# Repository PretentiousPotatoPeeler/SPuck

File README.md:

# PCB Parts

| Block | Part | JLCPCB |
| ------|------|--------|
| ESP32 | ESP32-S3-WROOM-1-N16R8 | [C2913202](https://jlcpcb.com/partdetail/3198300-ESP32_S3_WROOM_1N16R8/C2913202) |
| Mic 2X | SD18OB261-060 | [C2895290](https://jlcpcb.com/partdetail/Goertek-SD18OB261060/C2895290) |
| Amp   | MAX98357AETE+T | [C910544](https://jlcpcb.com/partdetail/978950-MAX98357AETET/C910544) |
| USB-C | HC-TYPE-C-16P-CH2.58-3A-02 | [C5307759](https://jlcpcb.com/partdetail/Hctl-HC_TYPE_C_16P_CH2_58_3A02/C5307759) |
| Power Regulation | AMS1117 | [C347222](https://jlcpcb.com/partdetail/323882-AMS1117_33/C347222) |
| Screw Terminal | XY308-2.54-2P | [C557685](https://jlcpcb.com/partdetail/Ningbo_Xinlaiya_elec-XY308_2_542P/C557685) |
| TVS | LESD5D5.0CT1G | [C383211](https://jlcpcb.com/partdetail/Lrc-LESD5D50CT1G/C383211) |

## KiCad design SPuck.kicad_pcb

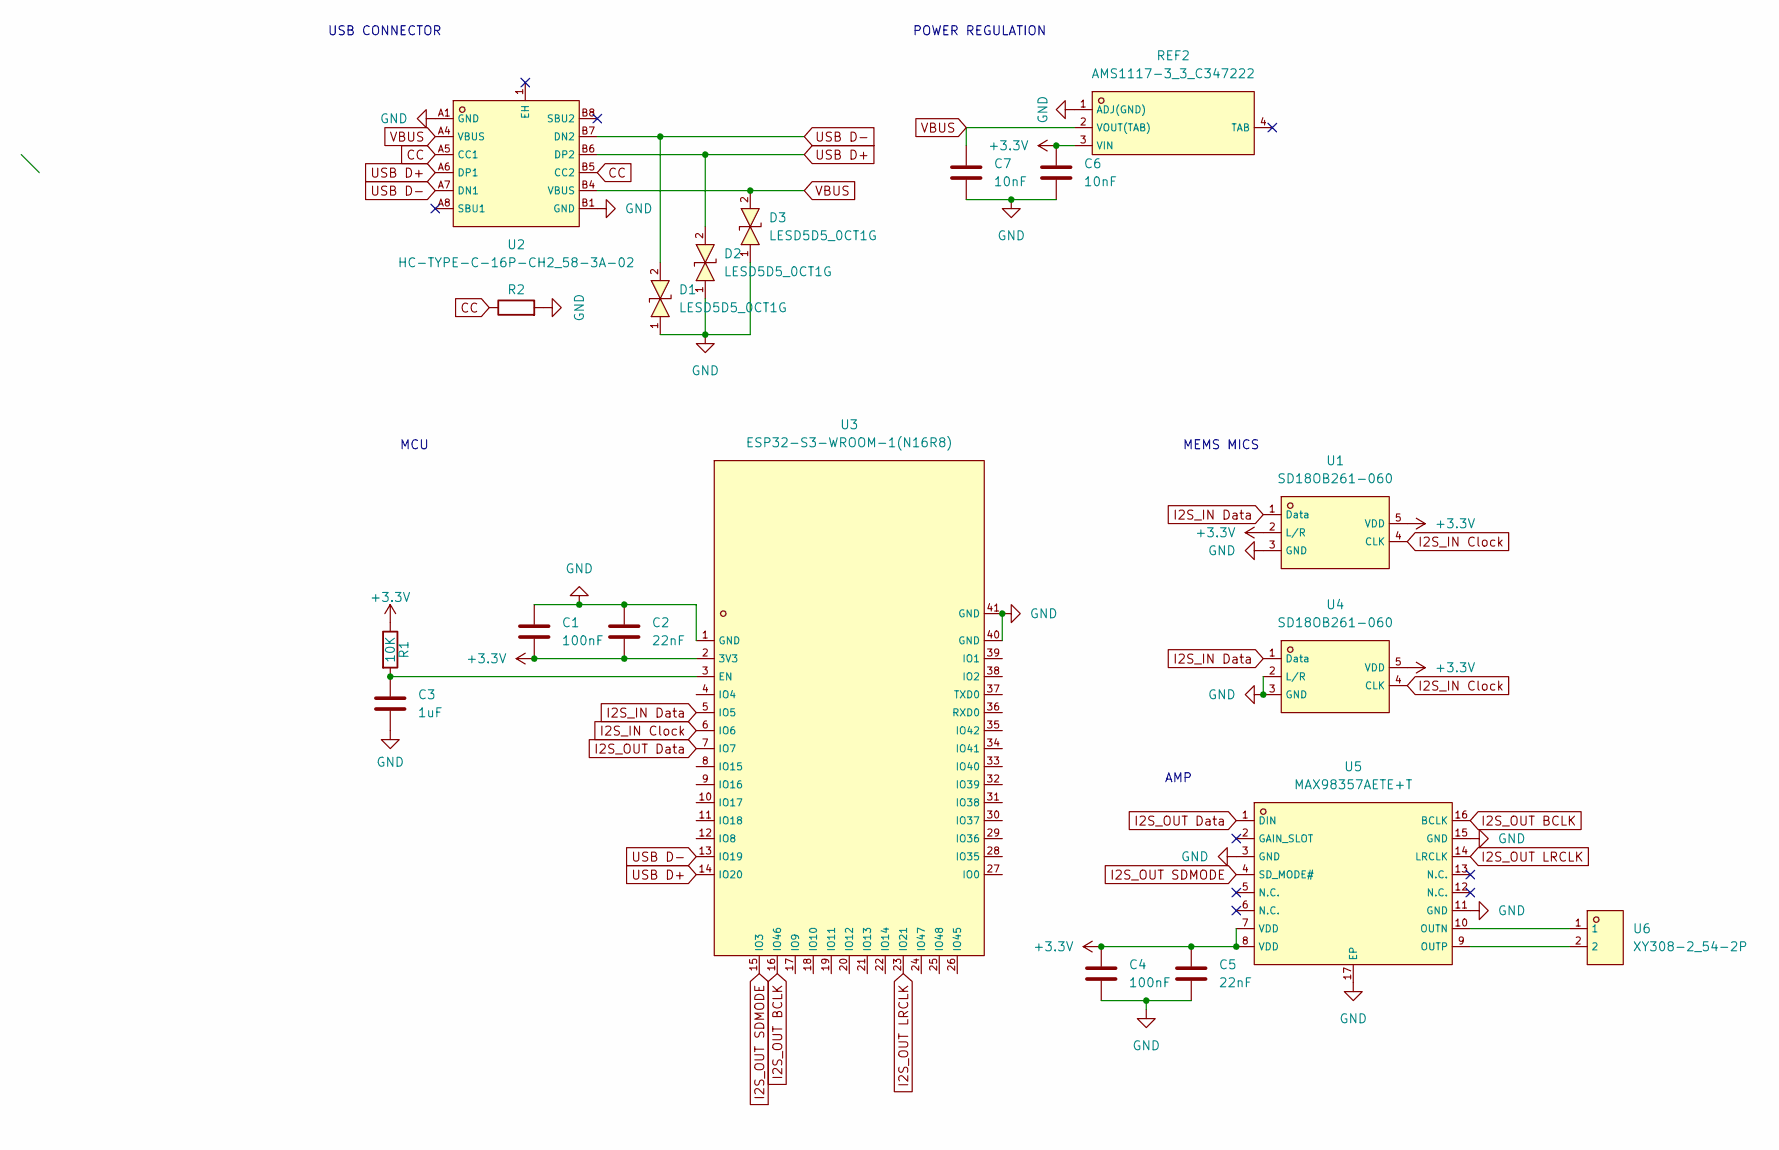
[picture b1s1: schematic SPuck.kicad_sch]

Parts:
C1, C4: 100nF; C_0402_1005Metric
C2, C5: 22nF; C_0402_1005Metric
C3: 1uF; C_0402_1005Metric
C6, C7: 10nF; C_0402_1005Metric
D1, D2, D3: LESD5D5_0CT1G; SOD-523_L1.2-W0.8-LS1.6-BI; LCSC C383211
R1: 10K; R_0402_1005Metric
R2: 5K1; R_0402_1005Metric
REF2: AMS1117-3_3_C347222; SOT-223-4_L6.5-W3.5-P2.30-LS7.0-BR; LCSC C347222
U1, U4: SD18OB261-060; MIC-SMD_SD18OB261-060; LCSC C2895290
U2: HC-TYPE-C-16P-CH2_58-3A-02; USB-C-SMD_HC-TYPE-C-16P-CH3.18-3A-02; LCSC C5307759
U3: ESP32-S3-WROOM-1(N16R8); WIRELM-SMD_ESP32-S3-WROOM-1; LCSC C2913202
U5: MAX98357AETE+T; TQFN-16_L3.0-W3.0-P0.50-BL-EP1.5; LCSC C910544
U6: XY308-2_54-2P; CONN-TH_XY308-2.54-2P; LCSC C557685

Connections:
+3.3V: C1.2, C2.2, C4.1, C5.1, C6.1, R1.1, REF2.3 (VIN), U1.2 (L/R), U1.5 (VDD), U3.2 (3V3), U4.5 (VDD), U5.7 (VDD), U5.8 (VDD)
CC: U2.A5 (CC1), U2.B5 (CC2); also elsewhere on the board
GND: C1.1, C2.1, C3.2, C4.2, C5.2, C6.2, C7.2, D1.1, D2.1, D3.1, REF2.1 (ADJ(GND)), U1.3 (GND), U2.A1 (GND), U2.B1 (GND), U3.1 (GND), U3.40 (GND), U3.41 (GND), U4.2 (L/R), U4.3 (GND), U5.3 (GND), U5.11 (GND), U5.15 (GND), U5.17 (EP); also elsewhere on the board
I2S_IN Clock: U1.4 (CLK), U3.6 (IO6), U4.4 (CLK)
I2S_IN Data: U1.1 (Data), U3.5 (IO5), U4.1 (Data)
I2S_OUT BCLK: U3.16 (IO46), U5.16 (BCLK)
I2S_OUT Data: U3.7 (IO7), U5.1 (DIN)
I2S_OUT LRCLK: U3.23 (IO21), U5.14 (LRCLK)
I2S_OUT SDMODE: U3.15 (IO3), U5.4 (SD_MODE#)
unnamed: C3.1, R1.2, U3.3 (EN)
unnamed: U5.10 (OUTN), U6.1
unnamed: U5.9 (OUTP), U6.2
USB D+: D2.2, U2.A6 (DP1), U2.B6 (DP2), U3.14 (IO20)
USB D-: D1.2, U2.A7 (DN1), U2.B7 (DN2), U3.13 (IO19)
VBUS: C7.1, D3.2, REF2.2 (VOUT(TAB)), U2.A4 (VBUS), U2.B4 (VBUS)

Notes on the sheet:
USB CONNECTOR
MCU
AMP
POWER REGULATION
MEMS MICS

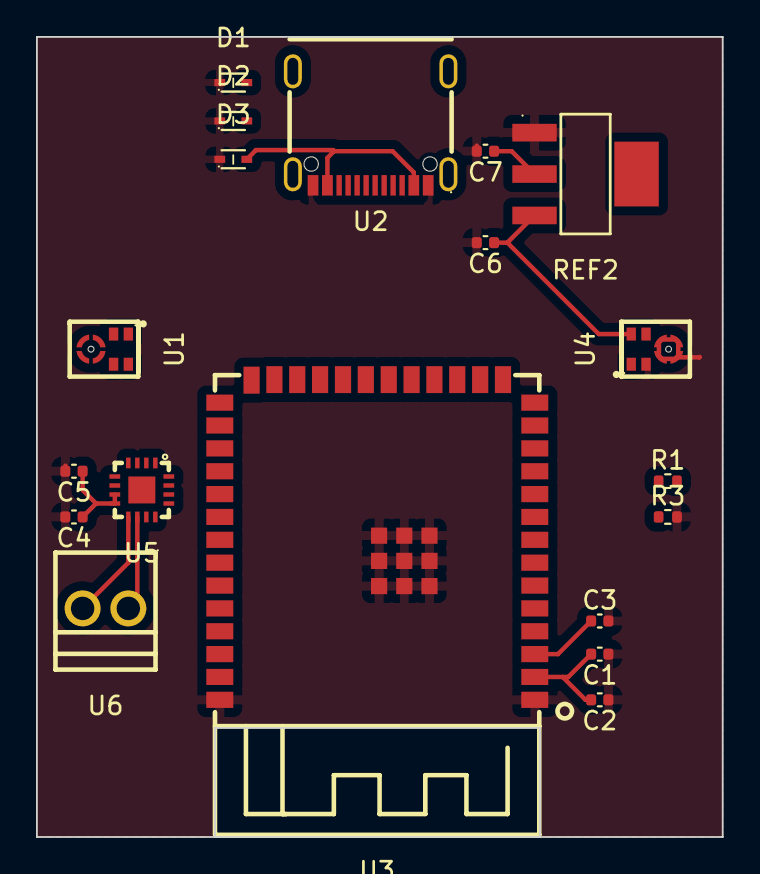
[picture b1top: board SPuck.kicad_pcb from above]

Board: 2 copper layers, 38.1 x 44.5 mm, 19 parts (0 on the bottom side), 15 nets.

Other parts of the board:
R3: 5K1; R_0402_1005Metric

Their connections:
CC: R3.1; also elsewhere on the board
GND: R3.2; also elsewhere on the board

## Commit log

2023-12-08 Schematic done, PCB WIP
